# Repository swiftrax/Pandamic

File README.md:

# Pandamic
A 65% mechanical keyboard with a rotary encoder and numpad moved to the left (not mirrored)

[Keyboard Layout Editor](http://www.keyboard-layout-editor.com/#/gists/109887f27b486985edc4fb8d0afd7937)

# Renders
Top PCB

Bottom PCB

*Made in KiCad 5.14*

## License

This repository is under the [GNU GPL V2 license](https://github.com/swiftrax/Pandamic/blob/master/LICENSE). If you plan to sell these pcbs, make sure to read it.

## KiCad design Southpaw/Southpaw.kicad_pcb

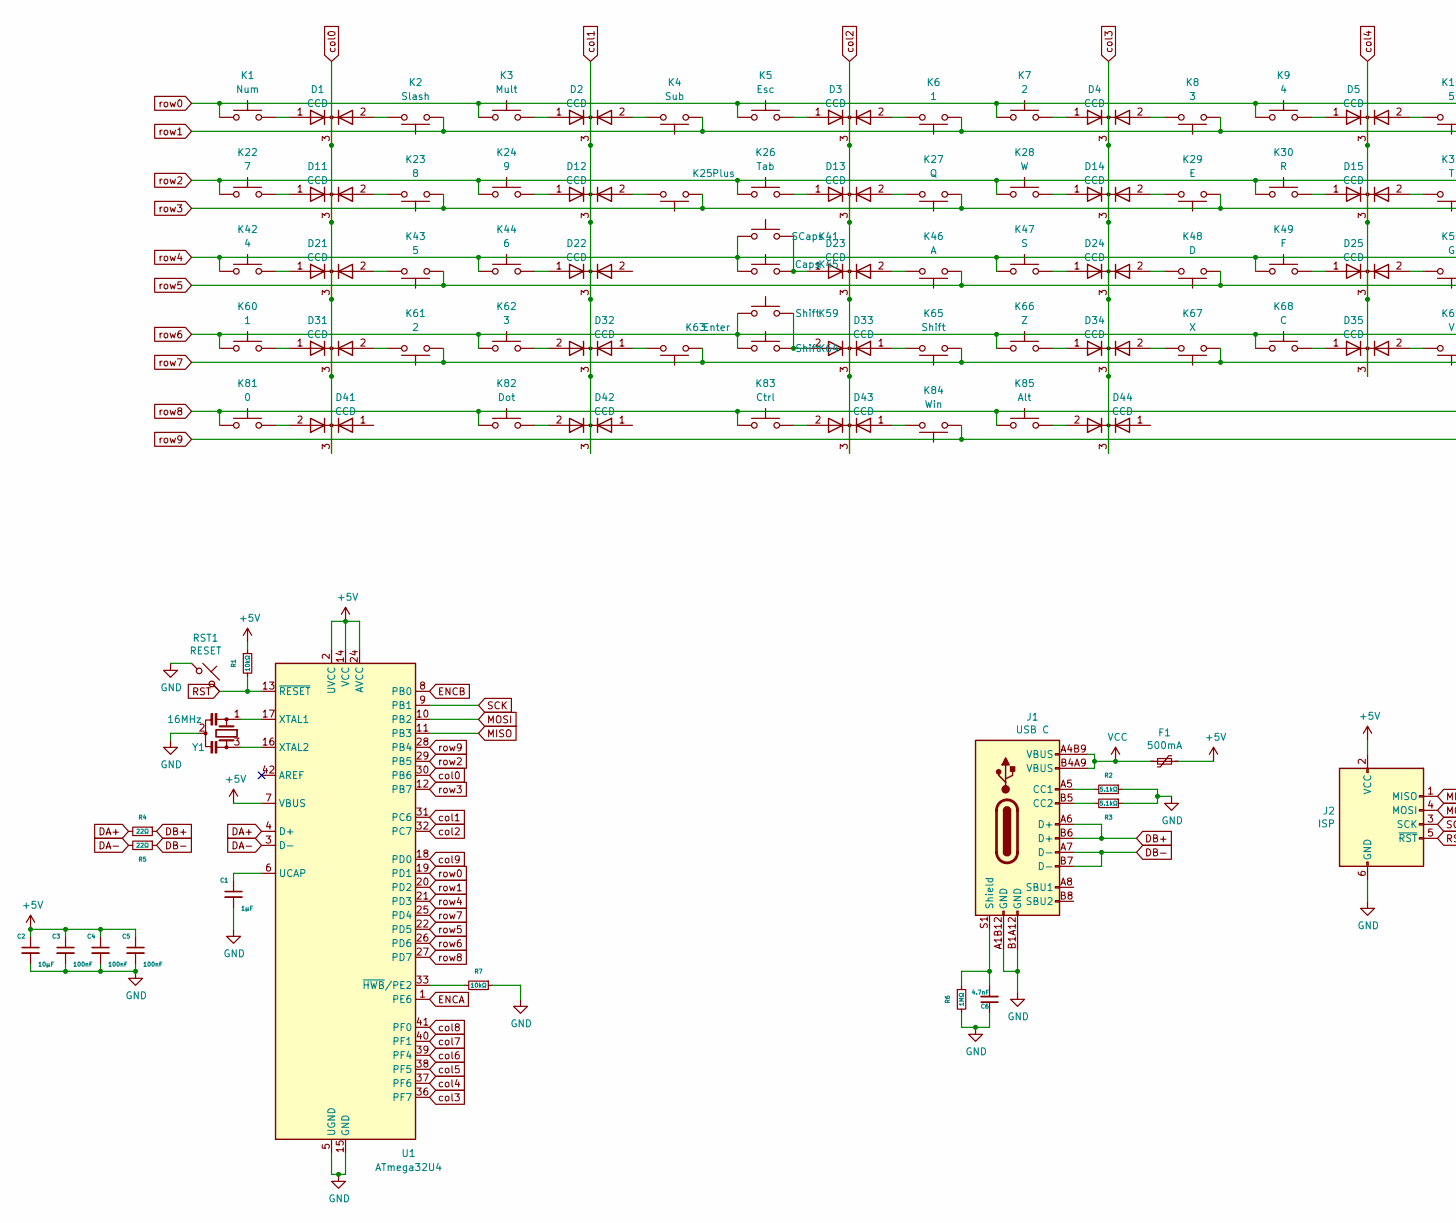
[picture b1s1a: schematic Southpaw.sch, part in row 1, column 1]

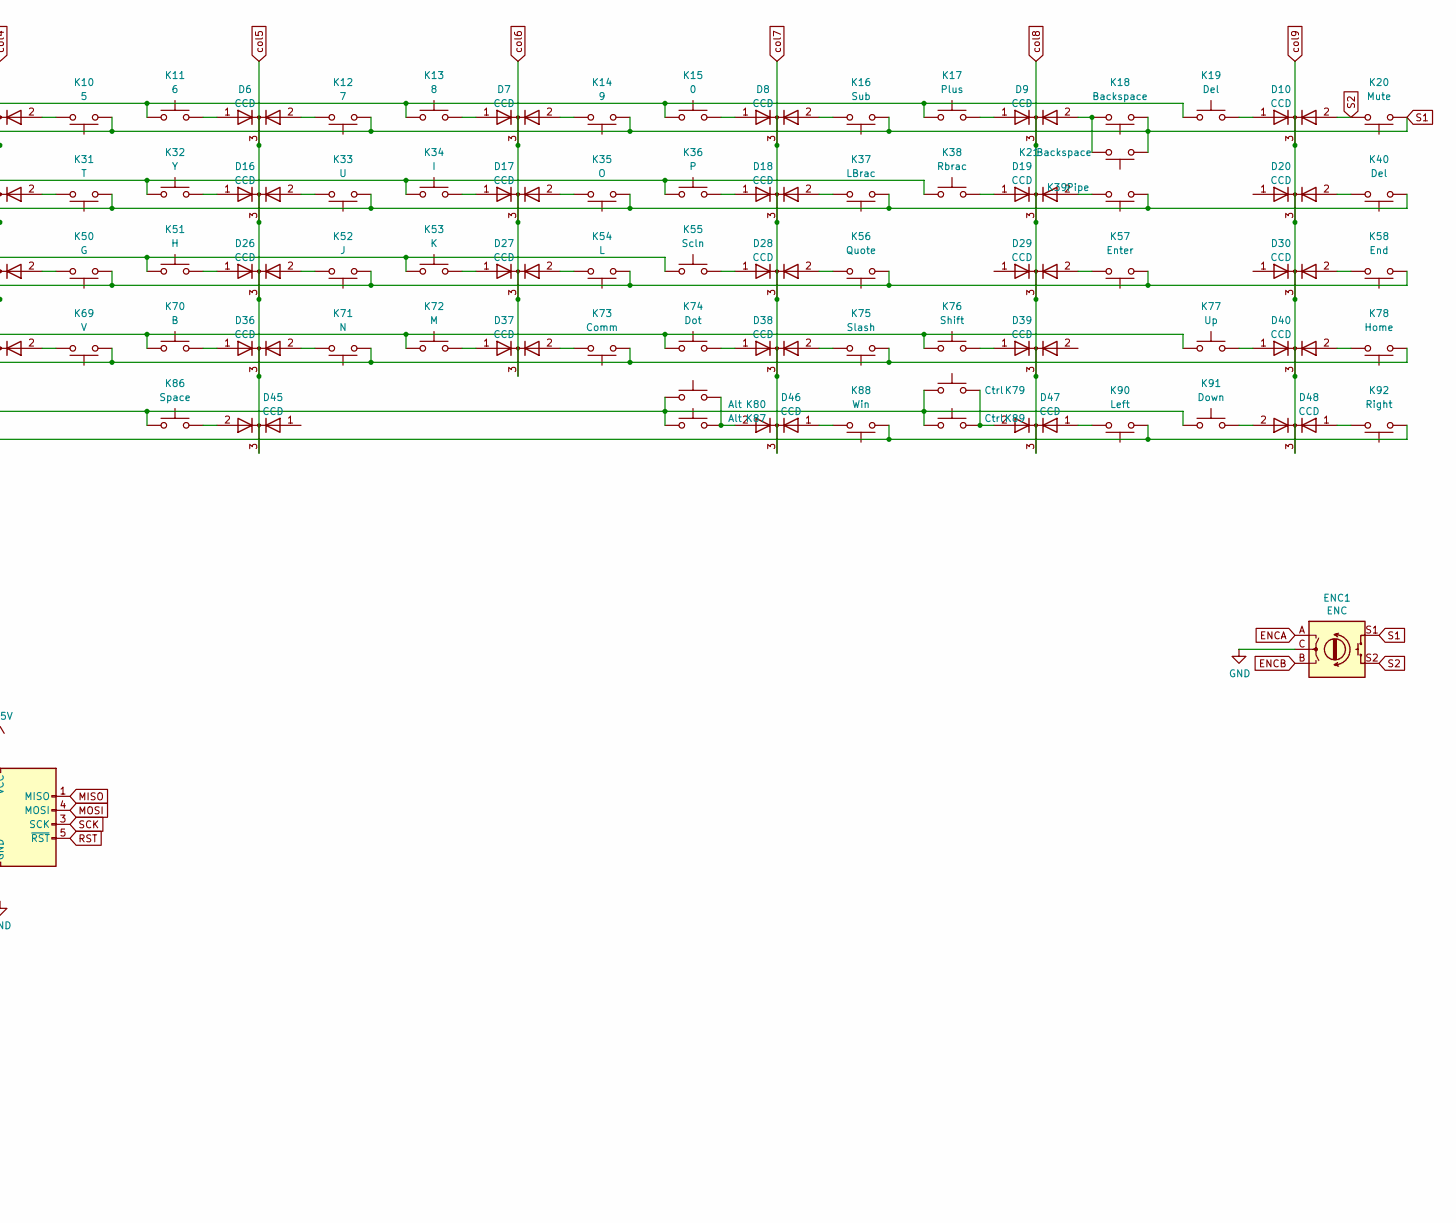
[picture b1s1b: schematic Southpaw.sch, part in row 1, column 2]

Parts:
C1: 1μF; C_0603_Annotated
C2: 10μF; C_0603_Annotated
C3, C4, C5: 100nF; C_0603_Annotated
C6: 4.7nF; C_0603_Annotated
D1, D2, D3, D4, D5, D6, D7, D8, D9, D10, D11, D12, D13, D14, D15, D16, D17, D18, D19, D20, D21, D22, D23, D24, D25, D26, D27, D28, D29, D30, D31, D32, D33, D34, D35, D36, D37, D38, D39, D40, D41, D42, D43, D44, D45, D46, D47, D48: CCD; SOT-23_Annotated
ENC1: ENC; Rotary_Encoder
F1: 500mA; Fuse_1206_Annotated
J1: USB C; Mid_Mount-USB_C_HandSoldering
J2: ISP; ISP_Header_Annotated
K1: Num; MXOnly-1U-NoLED
K2, K75: Slash; MXOnly-1U-NoLED
K3: Mult; MXOnly-1U-NoLED
K4, K16: Sub; MXOnly-1U-NoLED
K5: Esc; MXOnly-1U-NoLED
K6, K60: 1; MXOnly-1U-NoLED
K7, K61: 2; MXOnly-1U-NoLED
K8, K62: 3; MXOnly-1U-NoLED
K9, K42: 4; MXOnly-1U-NoLED
K10, K43: 5; MXOnly-1U-NoLED
K11, K44: 6; MXOnly-1U-NoLED
K12, K22: 7; MXOnly-1U-NoLED
K13, K23: 8; MXOnly-1U-NoLED
K14, K24: 9; MXOnly-1U-NoLED
K15: 0; MXOnly-1U-NoLED
K17: Plus; MXOnly-1U-NoLED
K18: Backspace; MXOnly-2U-NoLED
K19, K40: Del; MXOnly-1U-NoLED
K20: Mute; MXOnly-1U-NoLED
K21: Backspace; MXOnly-1U-NoLED
K25: Plus; MXOnly-2U-NoLED
K26: Tab; MXOnly-1.5U-NoLED
K27: Q; MXOnly-1U-NoLED
K28: W; MXOnly-1U-NoLED
K29: E; MXOnly-1U-NoLED
K30: R; MXOnly-1U-NoLED
K31: T; MXOnly-1U-NoLED
K32: Y; MXOnly-1U-NoLED
K33: U; MXOnly-1U-NoLED
K34: I; MXOnly-1U-NoLED
K35: O; MXOnly-1U-NoLED
K36: P; MXOnly-1U-NoLED
K37: LBrac; MXOnly-1U-NoLED
K38: Rbrac; MXOnly-1U-NoLED
K39: Pipe; MXOnly-1.5U-NoLED
K41: SCaps; MXOnly-1.25U-NoLED
K45: Caps; MXOnly-1.75U-NoLED
K46: A; MXOnly-1U-NoLED
K47: S; MXOnly-1U-NoLED
K48: D; MXOnly-1U-NoLED
K49: F; MXOnly-1U-NoLED
K50: G; MXOnly-1U-NoLED
K51: H; MXOnly-1U-NoLED
K52: J; MXOnly-1U-NoLED
K53: K; MXOnly-1U-NoLED
K54: L; MXOnly-1U-NoLED
K55: Scln; MXOnly-1U-NoLED
K56: Quote; MXOnly-1U-NoLED
K57: Enter; MXOnly-2.25U-NoLED
K58: End; MXOnly-1U-NoLED
K59: Shift; MXOnly-1.25U-NoLED
K63: Enter; MXOnly-2U-NoLED
K64: Shift; MXOnly-2.25U-NoLED
K65: Shift; MXOnly-1U-NoLED
K66: Z; MXOnly-1U-NoLED
K67: X; MXOnly-1U-NoLED
K68: C; MXOnly-1U-NoLED
K69: V; MXOnly-1U-NoLED
K70: B; MXOnly-1U-NoLED
K71: N; MXOnly-1U-NoLED
K72: M; MXOnly-1U-NoLED
K73: Comm; MXOnly-1U-NoLED
K74, K82: Dot; MXOnly-1U-NoLED
K76: Shift; MXOnly-1.75U-NoLED
K77: Up; MXOnly-1U-NoLED
K78: Home; MXOnly-1U-NoLED
K79: Ctrl; MXOnly-1.5U-NoLED
K80: Alt; MXOnly-1.5U-NoLED
K81: 0; MXOnly-2U-NoLED
K83: Ctrl; MXOnly-1.25U-NoLED
K84: Win; MXOnly-1.25U-NoLED
K85: Alt; MXOnly-1.25U-NoLED
K86: Space; MXOnly-6.25U-NoLED
K87: Alt; MXOnly-1U-NoLED
K88: Win; MXOnly-1U-NoLED
K89: Ctrl; MXOnly-1U-NoLED
K90: Left; MXOnly-1U-NoLED
K91: Down; MXOnly-1U-NoLED
K92: Right; MXOnly-1U-NoLED
R1, R7: 10kΩ; R_0603_Annotated
R2, R3: 5.1kΩ; R_0603_Annotated
R4, R5: 22Ω; R_0603_Annotated
R6: 1MΩ; R_0603_Annotated
RST1: RESET; Tactile_Switch
U1: ATmega32U4; ATMEGA32U4_Annotated
Y1: 16MHz; Resonator_3Pin_Annotated

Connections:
+5V: C2.1, C3.1, C4.1, C5.1, F1.1, J2.2 (VCC), R1.1, U1.2 (UVCC), U1.7 (VBUS), U1.14 (VCC), U1.24 (AVCC), U1.34 (VCC), U1.44 (AVCC)
DA+: R4.2, U1.4 (D+)
DA-: R5.2, U1.3 (D-)
DB+: J1.A6 (D+), J1.B6 (D+), R4.1
DB-: J1.A7 (D-), J1.B7 (D-), R5.1
ENCA: ENC1.A, U1.1 (PE6)
ENCB: ENC1.B, U1.8 (PB0)
GND: C1.2, C2.2, C3.2, C4.2, C5.2, C6.1, ENC1.C, J1.A1B12 (GND), J1.B1A12 (GND), J2.6 (GND), R2.1, R3.1, R6.2, R7.1, RST1.1, U1.5 (UGND), U1.15 (GND), U1.23 (GND), U1.35 (GND), U1.43 (GND), Y1.2
MISO: J2.1 (MISO), U1.11 (PB3)
MOSI: J2.4 (MOSI), U1.10 (PB2)
unnamed: C1.1, U1.6 (UCAP)
unnamed: C6.2, J1.S1 (Shield), R6.1
unnamed: D1.1 (A), K1.1
unnamed: D1.2 (A), K2.1
unnamed: D2.1 (A), K3.1
unnamed: D2.2 (A), K4.1
unnamed: D3.1 (A), K5.1
unnamed: D3.2 (A), K6.1
unnamed: D4.1 (A), K7.1
unnamed: D4.2 (A), K8.1
unnamed: D5.1 (A), K9.1
unnamed: D5.2 (A), K10.1
unnamed: D6.1 (A), K11.1
unnamed: D6.2 (A), K12.1
unnamed: D7.1 (A), K13.1
unnamed: D7.2 (A), K14.1
unnamed: D8.1 (A), K15.1
unnamed: D8.2 (A), K16.1
unnamed: D9.1 (A), K17.1
unnamed: D9.2 (A), K18.1, K21.1
unnamed: D10.1 (A), K19.1
unnamed: D11.1 (A), K22.1
unnamed: D11.2 (A), K23.1
unnamed: D12.1 (A), K24.1
unnamed: D12.2 (A), K25.1
unnamed: D13.1 (A), K26.1
unnamed: D13.2 (A), K27.1
unnamed: D14.1 (A), K28.1
unnamed: D14.2 (A), K29.1
unnamed: D15.1 (A), K30.1
unnamed: D15.2 (A), K31.1
unnamed: D16.1 (A), K32.1
unnamed: D16.2 (A), K33.1
unnamed: D17.1 (A), K34.1
unnamed: D17.2 (A), K35.1
unnamed: D18.1 (A), K36.1
unnamed: D18.2 (A), K37.1
unnamed: D19.1 (A), K38.1
unnamed: D19.2 (A), K39.1
unnamed: D20.2 (A), K40.1
unnamed: D21.1 (A), K42.1
unnamed: D21.2 (A), K43.1
unnamed: D22.1 (A), K44.1
unnamed: D23.1 (A), K41.1, K45.1
unnamed: D23.2 (A), K46.1
unnamed: D24.1 (A), K47.1
unnamed: D24.2 (A), K48.1
unnamed: D25.1 (A), K49.1
unnamed: D25.2 (A), K50.1
unnamed: D26.1 (A), K51.1
unnamed: D26.2 (A), K52.1
unnamed: D27.1 (A), K53.1
unnamed: D27.2 (A), K54.1
unnamed: D28.1 (A), K55.1
unnamed: D28.2 (A), K56.1
unnamed: D29.2 (A), K57.1
unnamed: D30.2 (A), K58.1
unnamed: D31.1 (A), K60.1
unnamed: D31.2 (A), K61.1
unnamed: D32.1 (A), K63.1
unnamed: D32.2 (A), K62.1
unnamed: D33.1 (A), K65.1
unnamed: D33.2 (A), K59.1, K64.1
unnamed: D34.1 (A), K66.1
unnamed: D34.2 (A), K67.1
unnamed: D35.1 (A), K68.1
unnamed: D35.2 (A), K69.1
unnamed: D36.1 (A), K70.1
unnamed: D36.2 (A), K71.1
unnamed: D37.1 (A), K72.1
unnamed: D37.2 (A), K73.1
unnamed: D38.1 (A), K74.1
unnamed: D38.2 (A), K75.1
unnamed: D39.1 (A), K76.1
unnamed: D40.1 (A), K77.1
unnamed: D40.2 (A), K78.1
unnamed: D41.2 (A), K81.1
unnamed: D42.2 (A), K82.1
unnamed: D43.1 (A), K84.1
unnamed: D43.2 (A), K83.1
unnamed: D44.2 (A), K85.1
unnamed: D45.2 (A), K86.1
unnamed: D46.1 (A), K88.1
unnamed: D46.2 (A), K80.1, K87.1
unnamed: D47.1 (A), K90.1
unnamed: D47.2 (A), K79.1, K89.1
unnamed: D48.1 (A), K92.1
unnamed: D48.2 (A), K91.1
unnamed: J1.A5 (CC1), R2.2
unnamed: J1.B5 (CC2), R3.2
unnamed: R7.2, U1.33 (~HWB~/PE2)
unnamed: U1.16 (XTAL2), Y1.3
unnamed: U1.17 (XTAL1), Y1.1
RST: J2.5 (~RST), R1.2, RST1.2, U1.13 (~RESET)
S1: ENC1.S1, K2.2, K4.2, K6.2, K8.2, K10.2, K12.2, K14.2, K16.2, K18.2, K20.2, K21.2, U1.20 (PD2)
S2: D10.2 (A), ENC1.S2, K20.1
SCK: J2.3 (SCK), U1.9 (PB1)
VCC: F1.2, J1.A4B9 (VBUS), J1.B4A9 (VBUS)
col0: D1.3 (K), D11.3 (K), D21.3 (K), D31.3 (K), D41.3 (K), U1.30 (PB6)
col1: D2.3 (K), D12.3 (K), D22.3 (K), D32.3 (K), D42.3 (K), U1.31 (PC6)
col2: D3.3 (K), D13.3 (K), D23.3 (K), D33.3 (K), D43.3 (K), U1.32 (PC7)
col3: D4.3 (K), D14.3 (K), D24.3 (K), D34.3 (K), D44.3 (K), U1.36 (PF7)
col4: D5.3 (K), D15.3 (K), D25.3 (K), D35.3 (K), U1.37 (PF6)
col5: D6.3 (K), D16.3 (K), D26.3 (K), D36.3 (K), D45.3 (K), U1.38 (PF5)
col6: D7.3 (K), D17.3 (K), D27.3 (K), D37.3 (K), U1.39 (PF4)
col7: D8.3 (K), D18.3 (K), D28.3 (K), D38.3 (K), D46.3 (K), U1.40 (PF1)
col8: D9.3 (K), D19.3 (K), D29.3 (K), D39.3 (K), D47.3 (K), U1.41 (PF0)
col9: D10.3 (K), D20.3 (K), D30.3 (K), D40.3 (K), D48.3 (K), U1.18 (PD0)
row0: K1.2, K3.2, K5.2, K7.2, K9.2, K11.2, K13.2, K15.2, K17.2, K19.2, U1.19 (PD1)
row2: K22.2, K24.2, K26.2, K28.2, K30.2, K32.2, K34.2, K36.2, K38.2, U1.29 (PB5)
row3: K23.2, K25.2, K27.2, K29.2, K31.2, K33.2, K35.2, K37.2, K39.2, K40.2, U1.12 (PB7)
row4: K41.2, K42.2, K44.2, K45.2, K47.2, K49.2, K51.2, K53.2, K55.2, U1.21 (PD3)
row5: K43.2, K46.2, K48.2, K50.2, K52.2, K54.2, K56.2, K57.2, K58.2, U1.22 (PD5)
row6: K59.2, K60.2, K62.2, K64.2, K66.2, K68.2, K70.2, K72.2, K74.2, K76.2, K77.2, U1.26 (PD6)
row7: K61.2, K63.2, K65.2, K67.2, K69.2, K71.2, K73.2, K75.2, K78.2, U1.25 (PD4)
row8: K79.2, K80.2, K81.2, K82.2, K83.2, K85.2, K86.2, K87.2, K89.2, K91.2, U1.27 (PD7)
row9: K84.2, K88.2, K90.2, K92.2, U1.28 (PB4)

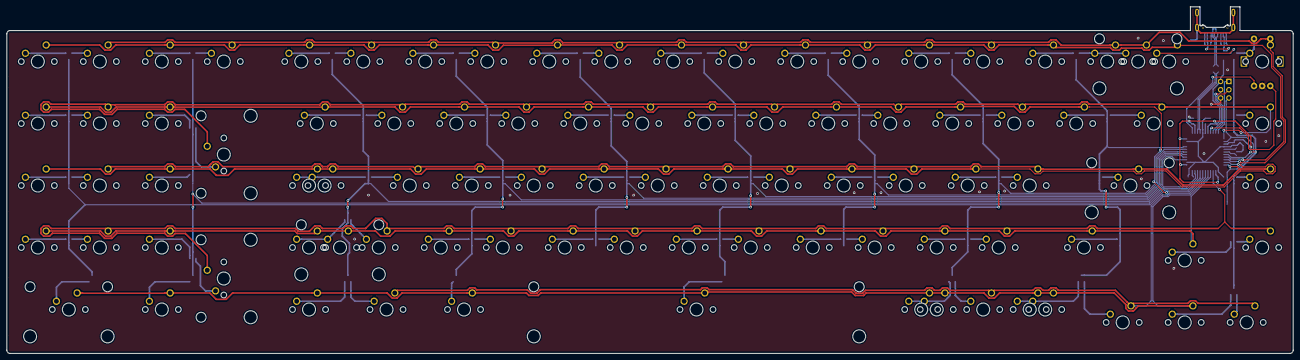
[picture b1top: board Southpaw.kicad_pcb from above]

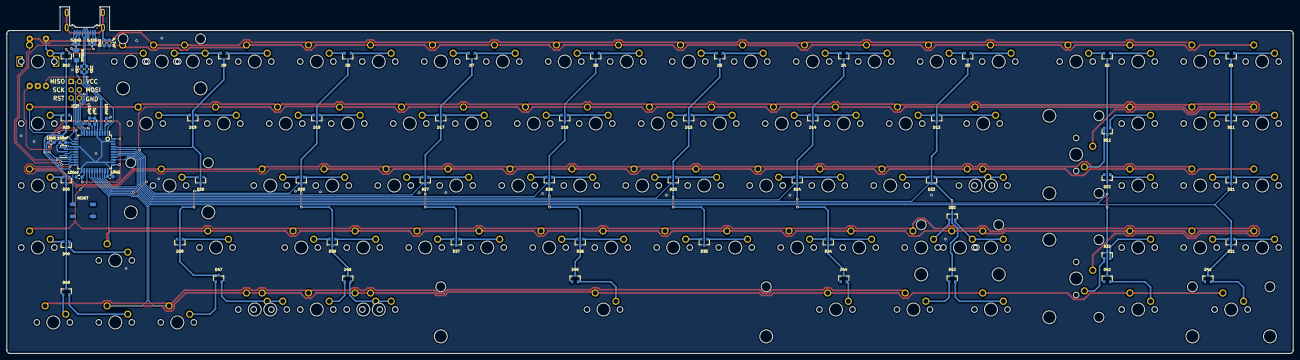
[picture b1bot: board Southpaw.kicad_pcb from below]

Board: 2 copper layers, 395.3 x 106.5 mm, 160 parts (67 on the bottom side), 127 nets.

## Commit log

2020-08-21 Duplex
2020-08-21 New footprints
2020-08-22 Layout
2020-08-22 Route
2020-08-23 Finish Routing
2020-08-23 Gerbers / Art
2020-09-04 Rename files
2020-09-04 Create LICENSE
2020-09-04 Update gerbers + add renders
2020-09-13 Move things into folders
